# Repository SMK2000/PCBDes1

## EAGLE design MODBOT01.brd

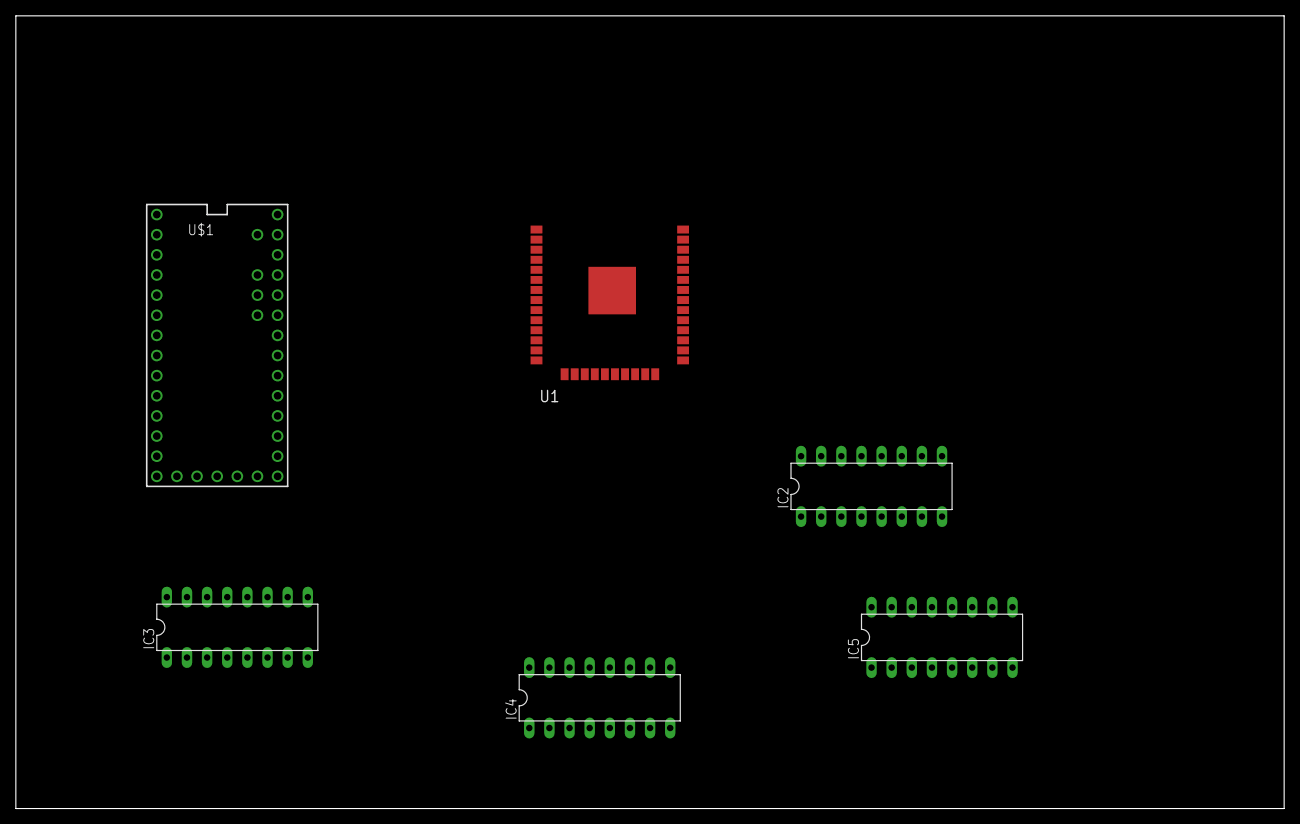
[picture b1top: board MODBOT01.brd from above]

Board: 2 copper layers, 160.0 x 100.0 mm, 6 parts (0 on the bottom side), 8 nets, no tracks yet.

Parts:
IC2, IC3, IC4, IC5: L293D; DIL16
U1: ESP-WROOM-32
U$1: TEENSY_3.1+4

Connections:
3.3V: U$1.3.3V, U$1.3.3V1
GND: U1.1, U1.15, U1.38, U1.GND, U$1.GND, U$1.GND1
GND1: IC2.4, IC3.4, IC4.4, IC5.4
GND2: IC2.5, IC3.5, IC4.5, IC5.5
GND3: IC2.13, IC3.13, IC4.13, IC5.13
GND4: IC2.12, IC3.12, IC4.12, IC5.12
VCC1: IC2.16, IC3.16, IC4.16, IC5.16
VCC2: IC2.8, IC3.8, IC4.8, IC5.8

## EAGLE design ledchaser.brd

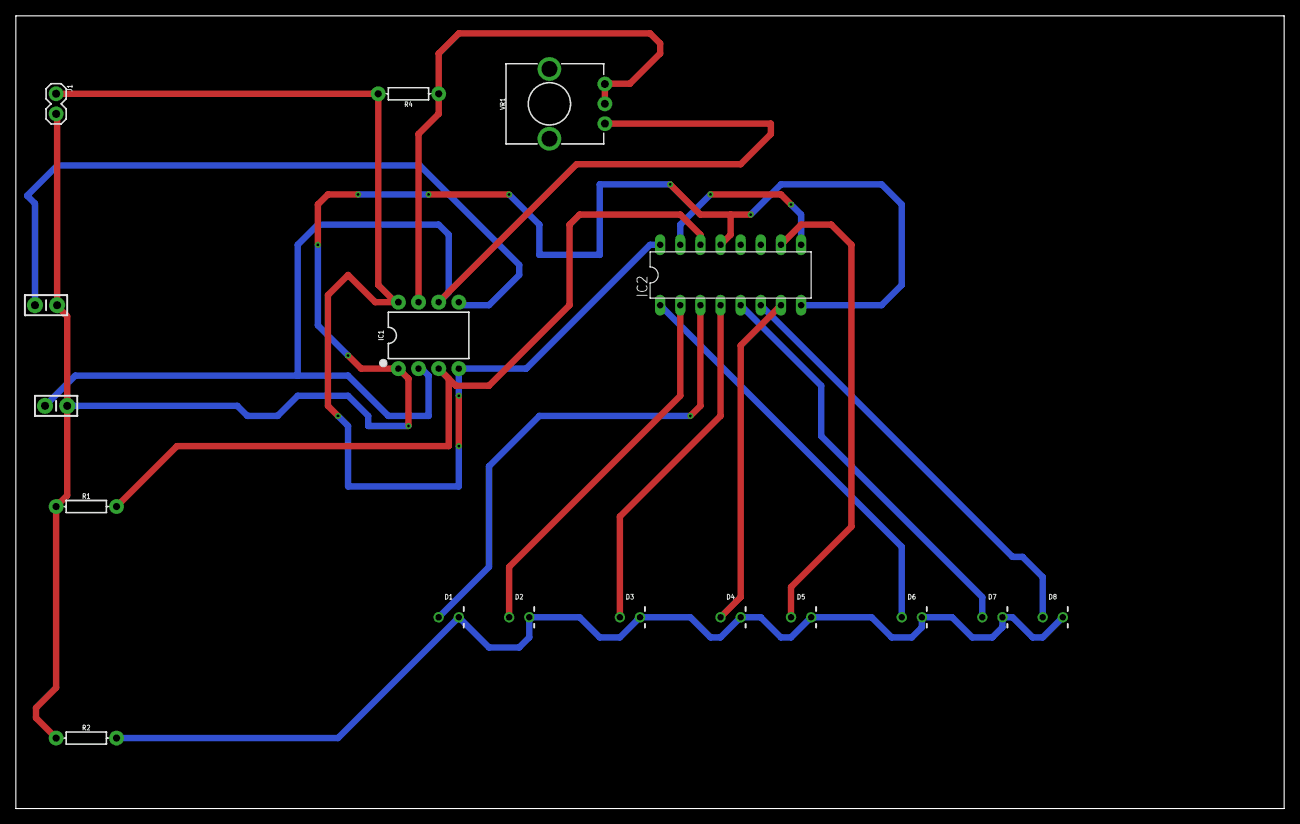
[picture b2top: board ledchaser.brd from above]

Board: 2 copper layers, 160.0 x 100.0 mm, 17 parts (0 on the bottom side), 16 nets.

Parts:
C1: 0.1uF; CAP-PTH-SMALL-KIT
C2: 0.01uF; CAP-PTH-SMALL-KIT
D1, D2, D3, D4, D5, D6, D7, D8: LED_3MM-NS
IC1: 555; DIP08-KIT
IC2: 4017N; DIL16
J1: 1X02
R1: 10k; AXIAL-0.3
R2: 100; AXIAL-0.3
R4: 1M; AXIAL-0.3
VR1: 1M; POT-PTH-ALPS-KIT

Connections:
12V: IC1.4, IC1.8, IC2.16, J1.1, R4.P$2
GND: C1.2, C2.2, IC1.1, IC2.8, IC2.13, J1.2, R1.P$1, R2.P$1
unnamed: C2.1, IC1.5
unnamed: C1.1, IC1.2, IC1.6, VR1.P$1
unnamed: IC1.7, R4.P$1, VR1.P$2, VR1.P$3
unnamed: IC1.3, IC2.14, R1.P$2
unnamed: D1.A, IC2.3
unnamed: D2.A, IC2.2
unnamed: IC2.9, IC2.15
unnamed: D3.A, IC2.4
unnamed: D4.A, IC2.7
unnamed: D5.A, IC2.10
unnamed: D6.A, IC2.1
unnamed: D7.A, IC2.5
unnamed: D8.A, IC2.6
unnamed: D1.K, D2.K, D3.K, D4.K, D5.K, D6.K, D7.K, D8.K, R2.P$2

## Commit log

2019-08-12 Add files via upload
    Current (crappy) version of the LED chaser board
2020-02-07 very very rough idea... no connections
2020-02-07 only certain components added

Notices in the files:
parts and their libraries:
esp32: Creative Commons Attribution-ShareAlike 4.0 International
SparkFun-Capacitors: Licensing: Creative Commons ShareAlike 4.0 International - https://creativecommons.org/licenses/by-sa/4.0
